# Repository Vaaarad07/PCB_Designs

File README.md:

# PCB Design Files

## Projects
- [About](#about)
- [Cyclometer](#cyclometer)
- [STM32F407 MVCU](#stm32f407-mvcu)
- [STM32F103 VCU](#stm32f103-vcu)
- [STM32F103 Inverter VCU](#stm32f103-inverter-vcu)
- [STM32F103 Test board](#stm32f103-test-board)

## About 
This repo contains the PCB files designed by [@Vaaarad07](https://github.com/Vaaarad07).
All of the designs are completely produced in KiCad 6, and each project directory contains the respective  KiCad schematic and layout files. All of the PCB projects are manufactured and tested for their respective functionalities.
I am open for any kind of feedback, suggestion or discussion.

## Cyclometer 
Cyclometer is a minimal dashhborad for bicycles used to accurately measure, store and display the speed, distance & time of the bike rides.
The board uses **STM32F446** controller.

## RP2040 

## STM32407-MVCU
This is a custom made ***4-layer*** board using ***STM32F407***, designed for [Vegapod Hyperloop](https://linktr.ee/vegapodhyperloop?fbclid=PAAabTRk45duWqCT2ES2nHaDbXQsYjndH2ZH-L-wuU1rlmgXJXES0c9xlna4E_aem_AQGd-q00TIai_09fVyH2A-mdNry7ZboQbuSte4yDi2yoPS_CXYrpFN4jU0P01uli4RE), a student team. The board is a part of a vehicle control system as the Master control Unit. The board connects to 5 separate vehicle control unit boards using DB9 cables and connectors over ***CAN bus***,which are responsible for handling their sub-system specific functions.
### Following are some of the features of the board : 
- 9-36V input power supply, which is divided into 2 separate buses of 5V and 3.3V respectively using power regulators
- 5 DB9 ports to connect the VCUs with CAN bus connections along with reserved GPIOs.
- DB9 port with RS232 to serial converter to connect an INS, [Pollux 2](https://aeronsystems.com/ins/pollux-2/) 
- On-board RF-transceiver mount.
- 7-segment display
- SD Card slot
- 5-pin Debugger/programmer headers.
- Hardware reset.
- ***UART, SPI, ADC, DAC, I2C*** Connections
- 10 user LEDs with power-on LEDs.

## STM32F103-VCU
This is a custom made 2-Layer board using 
***STM32F103***, designed for [Vegapod Hyperloop](https://linktr.ee/vegapodhyperloop?fbclid=PAAabTRk45duWqCT2ES2nHaDbXQsYjndH2ZH-L-wuU1rlmgXJXES0c9xlna4E_aem_AQGd-q00TIai_09fVyH2A-mdNry7ZboQbuSte4yDi2yoPS_CXYrpFN4jU0P01uli4RE), a student team. The board is a part of a vehicle control system as a vehicle control Unit. The board connects to the Master vehicle control unit using DB9 cable and connector over ***CAN bus*** 
### Following are some of the features of the board : 
- Powered through either the Master control unit (5V) or from on-board power input (7-36V) which is further divided into two separate buses of 5V and 3.3V respectively.
- Connects to the Master control unit over CAN bus and reserved GPIOs.
- 4-pin debugger/programmer header.
- 5 user LEDs
- Hardware reset
- ***UART, SPI, I2C, ADC*** ports.

## STM32F103-Inverter-VCU
This is a custom made 2-Layer board using 
***STM32F103***, designed for [Vegapod Hyperloop](https://linktr.ee/vegapodhyperloop?fbclid=PAAabTRk45duWqCT2ES2nHaDbXQsYjndH2ZH-L-wuU1rlmgXJXES0c9xlna4E_aem_AQGd-q00TIai_09fVyH2A-mdNry7ZboQbuSte4yDi2yoPS_CXYrpFN4jU0P01uli4RE), a student team. The board is a part of a vehicle control system as a vehicle control Unit responsible for control of the ***inverter sub-system***. The board connects to the Master vehicle control unit using DB9 cable and connector over ***CAN bus*** 
### Following are some of the features of the board : 
- Powered through either the Master control unit (5V) or from on-board power input (7-36V) which is further divided into two separate buses of 5V and 3.3V respectively.
- Connects to the Master control unit over CAN bus and reserved GPIOs.
- PWM headers connecting to the inverter driver circuit.
- 4-pin debugger/programmer header.
- Hardware reset.
- ***UART, SPI, I2C, ADC*** ports.

## STM32f103-Test-Board
This is a custom made 2-Layer board using the ***STM32F103*** , designed for [Vegapod Hyperloop](https://linktr.ee/vegapodhyperloop?fbclid=PAAabTRk45duWqCT2ES2nHaDbXQsYjndH2ZH-L-wuU1rlmgXJXES0c9xlna4E_aem_AQGd-q00TIai_09fVyH2A-mdNry7ZboQbuSte4yDi2yoPS_CXYrpFN4jU0P01uli4RE), a student team. The board is designed for testing procedures of various peripherals of the controller and verification of the designed architecture of a vehicle control system.
### Following are some of the features of the board :
- Powered through either the DB9 connector(5V) or the on-board power input (7-36V) which is further divided into two separate buses of 5V and 3.3V respectively.
- ***CAN, UART, SPI, I2C, ADC, PWM*** peripheral ports.
- 4-pin debugger/programmer header.
- 7-segment display
- Hardware reset.

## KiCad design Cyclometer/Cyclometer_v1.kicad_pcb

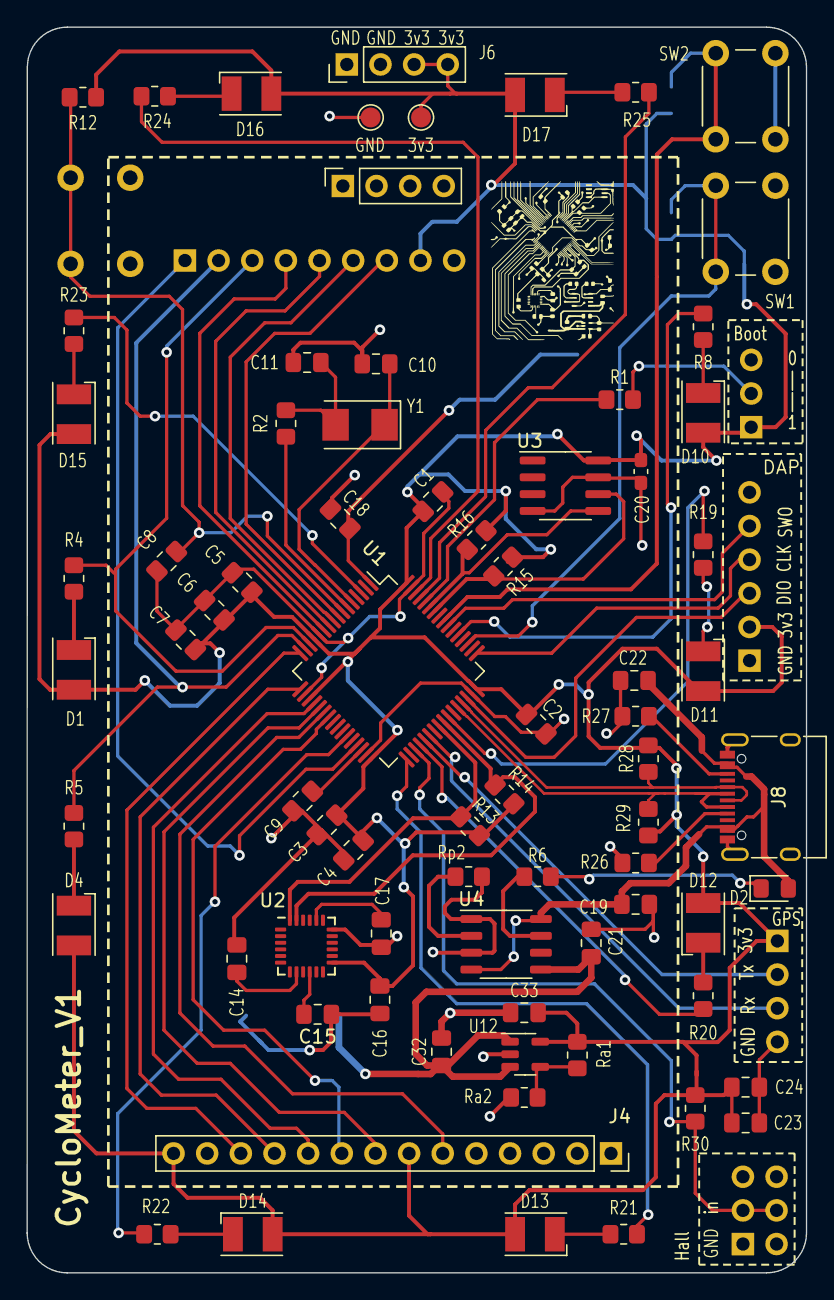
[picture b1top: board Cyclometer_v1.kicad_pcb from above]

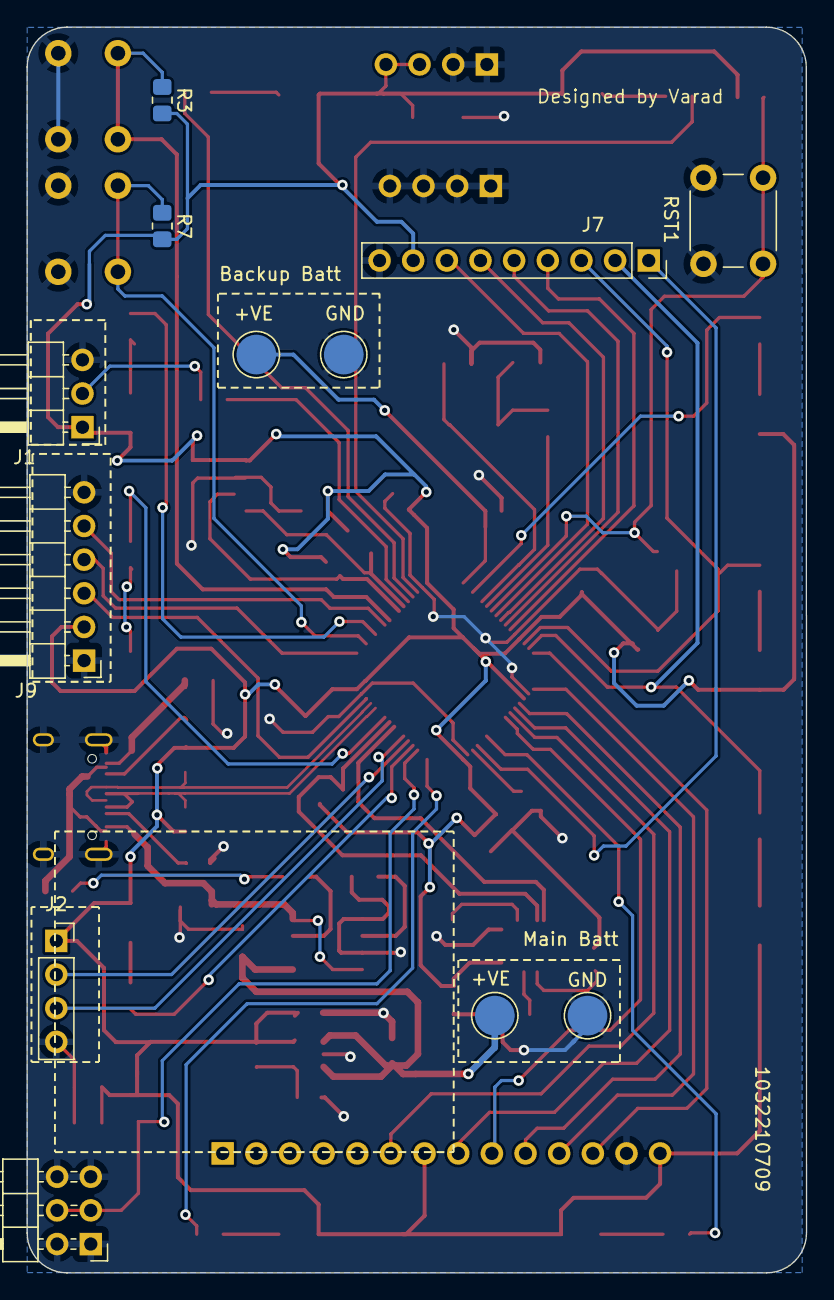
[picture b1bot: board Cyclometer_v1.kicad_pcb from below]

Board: 2 copper layers, 58.8 x 94.0 mm, 87 parts (12 on the bottom side), 66 nets.

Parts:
C1, C2, C3, C4, C5, C6, C8: 100nF; C_0805_2012Metric_Pad1.18x1.45mm_HandSolder
C7: 1uF; C_0805_2012Metric_Pad1.18x1.45mm_HandSolder
C9: 4.7uF; C_0805_2012Metric_Pad1.18x1.45mm_HandSolder
C10, C11: TBC; C_0805_2012Metric_Pad1.18x1.45mm_HandSolder
C14: 10nF; C_0805_2012Metric_Pad1.18x1.45mm_HandSolder
C15, C16, C19, C24: 0.1uF; C_0805_2012Metric_Pad1.18x1.45mm_HandSolder
C17: 2.2nF; C_0805_2012Metric_Pad1.18x1.45mm_HandSolder
C18, C21, C22, C23, C32, C33: 10uF; C_0805_2012Metric_Pad1.18x1.45mm_HandSolder
C20: 100nF; C_0603_1608Metric_Pad1.08x0.95mm_HandSolder
D1, D4, D10, D11, D12, D13, D14, D15, D16, D17: LED; LED_PLCC-2_3.4x3.0mm_KA
D2: LED; LED_0805_2012Metric_Pad1.15x1.40mm_HandSolder
J1: Conn_01x03_Male; PinHeader_1x03_P2.54mm_Horizontal
J2: GPS; PinSocket_1x04_P2.54mm_Vertical
J3: Conn_01x06_Pin; PinHeader_2x03_P2.54mm_Horizontal
J4: LCD; PinSocket_1x14_P2.54mm_Vertical
J5: LCD; PinSocket_1x04_P2.54mm_Vertical
J6: PinHeader_1x04_P2.54mm_Vertical
J7: NRF; PinSocket_1x09_P2.54mm_Vertical
J8: USB_C_Receptacle; USB_C_Receptacle_XKB_U262-16XN-4BVC11
J9: Conn_01x06_Pin; PinHeader_1x06_P2.54mm_Horizontal
R1, R3, R4, R5, R7, R8, R12, R19, R20, R21, R22, R23, R24, R25, R30: 10K; R_0805_2012Metric_Pad1.20x1.40mm_HandSolder
R2: TBC; R_0805_2012Metric_Pad1.20x1.40mm_HandSolder
R6: R_Small_US; R_0805_2012Metric_Pad1.20x1.40mm_HandSolder
R13, R14, R15, R16: 4.7k; R_0805_2012Metric_Pad1.20x1.40mm_HandSolder
R26, R27, R28, R29: 5.1k; R_0805_2012Metric_Pad1.20x1.40mm_HandSolder
RST1: SW_Push; SW_PUSH_6mm
Ra1, Ra2: R_Small_US; R_0805_2012Metric_Pad1.20x1.40mm_HandSolder
Rp2: 1K2; R_0805_2012Metric_Pad1.20x1.40mm_HandSolder
SW1, SW2: SW_Push; SW_PUSH_6mm
TP1, TP4: +VE; TestPoint_Pad_D3.0mm
TP2, TP3: GND; TestPoint_Pad_D3.0mm
TP5: GND; TestPoint_Pad_D1.5mm
TP6: 3v3; TestPoint_Pad_D1.5mm
U1: STM32F446RCTx; LQFP-64_10x10mm_P0.5mm
U2: MPU-6050; InvenSense_QFN-24_4x4mm_P0.5mm
U3: AT24CS32-SSHM; SOIC-8_3.9x4.9mm_P1.27mm
U4: TP4056; SOP-8_3.9x4.9mm_P1.27mm
U12: LDK130-ADJ_SOT23_SOT353; SOT-23-5
Y1: Crystal; Crystal_SMD_5032-2Pin_5.0x3.2mm

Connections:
+3.3V: C1.1, C2.1, C3.1, C4.1, C5.1, C6.1, C7.1, C16.2, C20.2, C23.2, C24.1, C33.2, D1.2 (A), D4.2 (A), D10.2 (A), D11.2 (A), D12.2 (A), D13.2 (A), D14.2 (A), D15.2 (A), D16.2 (A), D17.2 (A), J1.1, J2.1, J4.7, J4.14, J6.3, J6.4, J7.8, J9.2, R3.2, R7.2, R12.2, R13.2, R14.2, R15.2, R16.2, R28.2, R29.2, R30.2, Ra1.1, TP6.1, U1.13 (VDDA), U1.19 (VDD), U1.32 (VDD), U1.48 (VDD), U1.64 (VDD), U2.13 (VDD), U3.8 (VCC), U12.5 (OUT)
/MCU/EEPROM_SCL_1: R15.1, U1.58 (PB6), U3.6 (SCL)
/MCU/EEPROM_SDA_1: R16.1, U1.59 (PB7), U3.5 (SDA)
/MCU/GPS_1_Rx: J2.3, U1.38 (PC7)
/MCU/GPS_1_Tx: J2.2, U1.37 (PC6)
/MCU/HSE_IN: C10.1, U1.5 (PH0), Y1.1
/MCU/HSE_OUT: R2.2, U1.6 (PH1)
/MCU/HallEffect_ip: J3.3, J3.4, R30.1, U1.35 (PB14)
/MCU/IMU_SCL: R14.1, U1.41 (PA8), U2.23 (SCL)
/MCU/IMU_SDA: R13.1, U1.40 (PC9), U2.24 (SDA)
/MCU/LCD_Cs: J4.12, U1.16 (PA2)
/MCU/LCD_DcRs: J4.10, U1.20 (PA4)
/MCU/LCD_Miso: J4.6, U1.22 (PA6)
/MCU/LCD_Mosi: J4.9, U1.23 (PA7)
/MCU/LCD_Sck: J4.8, U1.21 (PA5)
/MCU/LCD_rst: J4.11, U1.17 (PA3)
/MCU/LED1: R8.1, U1.53 (PC12)
/MCU/LED2: R19.1, U1.42 (PA9)
/MCU/LED3: R20.1, U1.36 (PB15)
/MCU/LED4: R21.1, U1.33 (PB12)
/MCU/LED5: R22.1, U1.27 (PB1)
/MCU/LED8: R23.1, U1.3 (PC14)
/MCU/LED9: R24.1, U1.62 (PB9)
/MCU/LED10: R25.1, U1.61 (PB8)
/MCU/NRF_MISO_2: J7.5, U1.10 (PC2)
/MCU/NRF_MOSI2: J7.6, U1.9 (PC1)
/MCU/NRF_RDYN: J7.4, U1.11 (PC3)
/MCU/NRF_REQN: J7.7, U1.8 (PC0)
/MCU/NRF_SCK2: J7.1, U1.29 (PB10)
/MCU/NRF_UART_RX: J7.2, R5.1, U1.15 (PA1)
/MCU/NRF_UART_TX: J7.3, R4.1, U1.14 (PA0)
/MCU/SWCLK: J9.4, U1.49 (PA14)
/MCU/SWDIO: J9.3, U1.46 (PA13)
/MCU/SWO: J9.5, U1.55 (PB3)
/MCU/user_1: R7.1, SW1.1, U1.51 (PC10)
/MCU/user_2: R3.1, SW2.1, U1.56 (PB4)
/Power/USB_CC1: J8.B5 (CC2), R27.2
/Power/USB_CC2: J8.A5 (CC1), R26.2
Batt+: C21.1, C32.1, TP1.1, U4.5 (BAT), U12.1 (IN), U12.3 (EN)
GND: C1.2, C2.2, C3.2, C4.2, C5.2, C6.2, C7.2, C8.2, C9.2, C10.2, C11.2, C14.1, C15.1, C16.1, C17.1, C18.1, C19.2, C20.1, C21.2, C22.2, C23.1, C24.2, C32.2, C33.1, J1.3, J2.4, J3.1, J3.2, J3.5, J3.6, J4.13, J5.1, J5.2, J5.3, J5.4, J6.1, J6.2, J7.9, J8.A1 (GND), J8.A12 (GND), J8.B1 (GND), J8.B12 (GND), J8.S1 (SHIELD), J9.1, J9.6, R26.1, R27.1, RST1.1, Ra2.2, Rp2.1, SW1.2, SW2.2, TP2.1, TP3.1, TP5.1, U1.12 (VSSA), U1.18 (VSS), U1.31 (VSS), U1.47 (VSS), U1.63 (VSS), U2.18 (GND), U3.4 (GND), U3.7 (WP), U4.1 (Temp1), U4.3 (GND3), U12.2 (GND)
unnamed: C11.1, R2.1, Y1.2
unnamed: D1.1 (K), R4.2
unnamed: C19.1, C22.1, D2.2 (A), J8.A4 (VBUS), J8.A9 (VBUS), J8.B4 (VBUS), J8.B9 (VBUS), U4.4 (Vcc4), U4.8 (CE)
unnamed: D2.1 (K), R6.1
unnamed: D4.1 (K), R5.2
unnamed: D10.1 (K), R8.2
unnamed: D11.1 (K), R19.2
unnamed: D12.1 (K), R20.2
unnamed: D13.1 (K), R21.2
unnamed: D14.1 (K), R22.2
unnamed: D15.1 (K), R23.2
unnamed: D16.1 (K), R24.2
unnamed: D17.1 (K), R25.2
unnamed: J1.2, R1.1
unnamed: R1.2, U1.60 (BOOT0)
unnamed: C8.1, R12.1, RST1.2, U1.7 (NRST)
unnamed: C9.1, U1.30 (VCAP_1)
unnamed: C17.2, U2.20 (CPOUT)
unnamed: C15.2, U2.10 (REGOUT)
unnamed: C14.2, U2.8 (VLOGIC)
unnamed: R6.2, U4.7 (CHRG)
unnamed: Rp2.2, U4.2 (prog2)
unnamed: Ra1.2, Ra2.1, U12.4 (ADJ)
USB_FS_D+: J8.A6 (D+), J8.B6 (D+), R28.1, U1.45 (PA12)
USB_FS_D-: J8.A7 (D-), J8.B7 (D-), R29.1, U1.44 (PA11)
Vbat: C18.2, TP4.1, U1.1 (VBAT)

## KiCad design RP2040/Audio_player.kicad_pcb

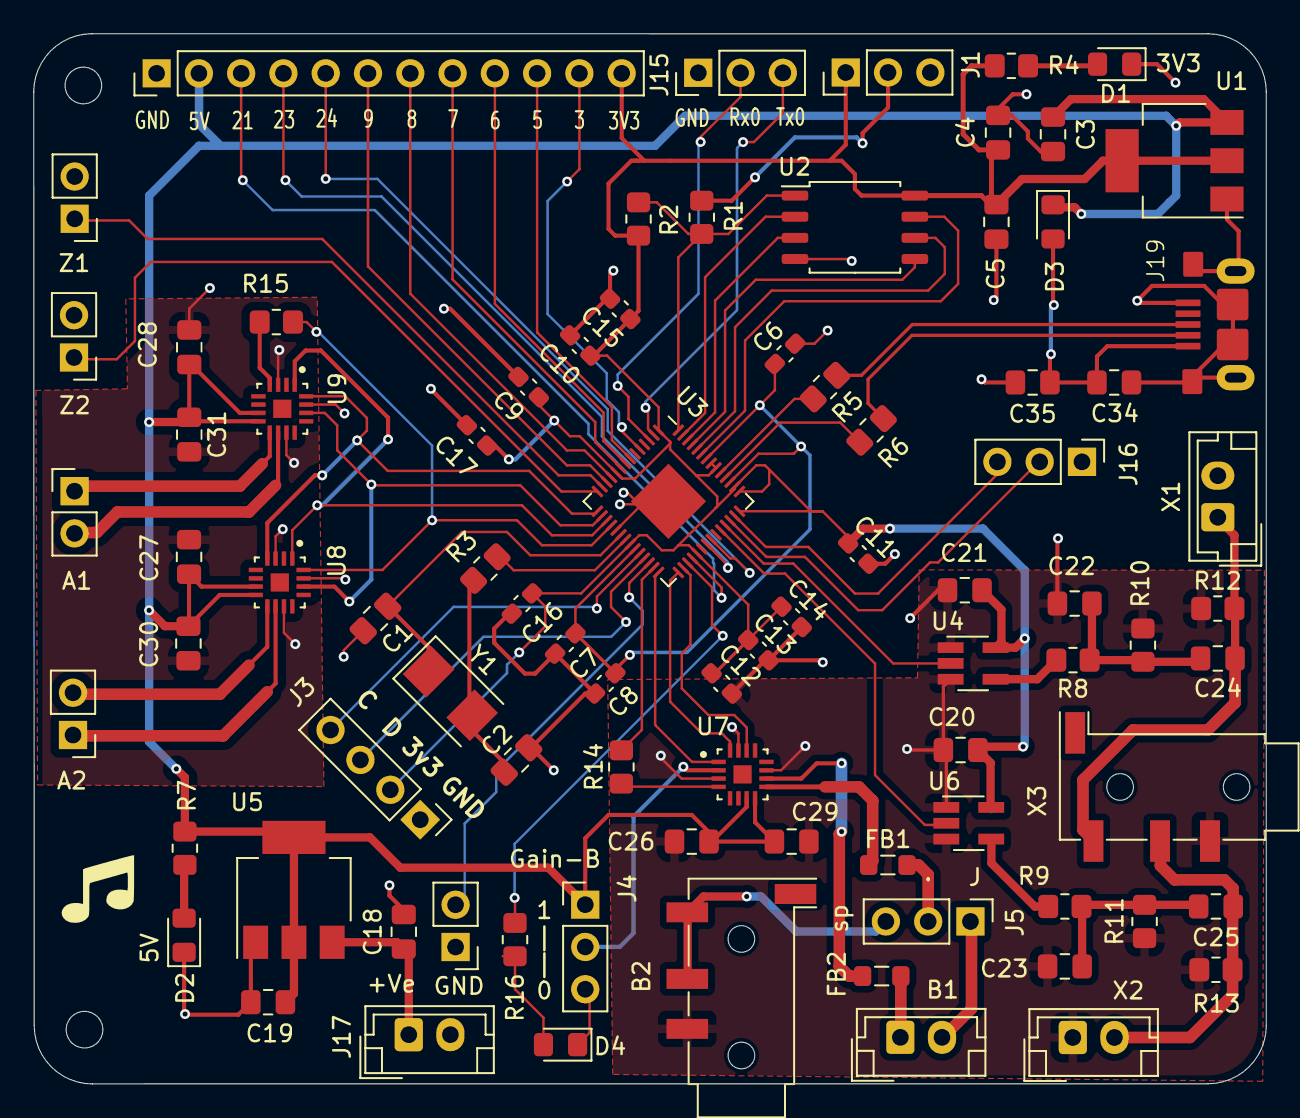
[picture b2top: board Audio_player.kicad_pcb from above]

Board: 2 copper layers, 74.0 x 63.1 mm, 86 parts (0 on the bottom side), 71 nets.

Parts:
A1, A2: Conn_01x02_Pin; PinHeader_1x02_P2.54mm_Vertical
B1: Conn_01x02_Pin; JST_EH_B2B-EH-A_1x02_P2.50mm_Vertical
B2: AudioJack4; Jack_3.5mm_KoreanHropartsElec_PJ-320D-4A_Horizontal
C1, C2, C5, C22, C23, C34: 100n; C_0805_2012Metric_Pad1.18x1.45mm_HandSolder
C3, C4, C18, C19, C20, C21, C26, C27, C28, C35: 10u; C_0805_2012Metric_Pad1.18x1.45mm_HandSolder
C6, C8, C9, C10, C12, C13, C14, C15, C16, C17: 100n; C_0603_1608Metric_Pad1.08x0.95mm_HandSolder
C7, C11: 1u; C_0603_1608Metric_Pad1.08x0.95mm_HandSolder
C24, C25: 47u; C_0805_2012Metric_Pad1.18x1.45mm_HandSolder
C29, C30, C31: 0.1u; C_0805_2012Metric_Pad1.18x1.45mm_HandSolder
D1, D2, D4: LED; LED_0805_2012Metric_Pad1.15x1.40mm_HandSolder
D3: D; D_0805_2012Metric_Pad1.15x1.40mm_HandSolder
FB1, FB2: FerriteBead_Small; L_0805_2012Metric_Pad1.05x1.20mm_HandSolder
H1, H4: MountingHole_Pad; MountingHole_2.2mm_M2
J1, J4, J5, J15, J16: Conn_01x03_Pin; PinHeader_1x03_P2.54mm_Vertical
J2: Conn_01x12_Pin; PinHeader_1x12_P2.54mm_Vertical
J3: Conn_01x04_Pin; PinHeader_1x04_P2.54mm_Vertical
J6: Conn_01x02_Pin; PinHeader_1x02_P2.54mm_Vertical
J17: Conn_01x02_Pin; JST_EH_B2B-EH-A_1x02_P2.50mm_Vertical
J19: USB3076-XX-X_REVC5; USB-B_varad
R1, R3, R4, R7, R16: 1k; R_0805_2012Metric_Pad1.20x1.40mm_HandSolder
R2: DNF; R_0805_2012Metric_Pad1.20x1.40mm_HandSolder
R5, R6: 27.4; R_0805_2012Metric_Pad1.20x1.40mm_HandSolder
R8, R9: 220; R_0805_2012Metric_Pad1.20x1.40mm_HandSolder
R10, R11: 100; R_0805_2012Metric_Pad1.20x1.40mm_HandSolder
R12, R13: 1.8k; R_0805_2012Metric_Pad1.20x1.40mm_HandSolder
R14: 300k; R_0805_2012Metric_Pad1.20x1.40mm_HandSolder
R15: 69.8k; R_0805_2012Metric_Pad1.20x1.40mm_HandSolder
U1: AMS1117-3.3; SOT-223-3_TabPin2
U2: W25Q128JVS; SOIC-8_5.23x5.23mm_P1.27mm
U3: RP2040; QFN-56-1EP_7x7mm_P0.4mm_EP3.2x3.2mm
U4, U6: 74LVC1G125; SOT-23-5_HandSoldering
U5: AMS1117-5.0; SOT-223-3_TabPin2
U7, U8, U9: MAX98357AETE_; QFN50P300X300X80-17N
X1, X2: Conn_01x02_Pin; JST_EH_B2B-EH-A_1x02_P2.50mm_Vertical
X3: AudioJack4; Jack_3.5mm_KoreanHropartsElec_PJ-320D-4A_Horizontal
Y1: Crystal; Crystal_SMD_5032-2Pin_5.0x3.2mm
Z1, Z2: Conn_01x02_Pin; PinHeader_1x02_P2.54mm_Vertical

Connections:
+3V3: C4.1, C5.1, C9.1, C10.1, C11.1, C12.1, C13.1, C14.1, C15.1, C16.1, C17.1, C20.1, C21.1, J1.1, J2.12, J3.2, R2.2, R4.1, U1.2 (VO), U2.8 (VCC), U3.1 (IOVDD), U3.10 (IOVDD), U3.22 (IOVDD), U3.33 (IOVDD), U3.42 (IOVDD), U3.43 (ADC_AVDD), U3.44 (VREG_IN), U3.48 (USB_VDD), U3.49 (IOVDD), U4.5 (VCC), U6.5 (VCC)
+5V: C3.1, C19.1, C26.1, C27.1, C28.1, C29.1, C30.1, C31.1, D3.1 (K), J2.2, J4.1, R7.1, U1.3 (VI), U5.2 (VO), U7.7 (VDD), U7.8 (VDD), U8.7 (VDD), U8.8 (VDD), U9.7 (VDD), U9.8 (VDD)
+BATT: C18.1, J17.1, U5.3 (VI)
/mcu/ADC0: U3.38 (GPIO26_ADC0), U6.2
/mcu/ADC1: U3.39 (GPIO27_ADC1), U4.2
/mcu/ADC2: J16.2, U3.40 (GPIO28_ADC2)
/mcu/ADC3: J16.3, U3.41 (GPIO29_ADC3)
/mcu/BCLK_1_19: U3.29 (GPIO18), U7.16 (BCLK)
/mcu/BCLK_2_12: U3.15 (GPIO12), U8.4 (~SD_MODE), U9.16 (BCLK)
/mcu/Din_1_17: U3.28 (GPIO17), U7.1 (DIN)
/mcu/Din_2_14: U3.17 (GPIO14), U8.1 (DIN), U9.1 (DIN)
/mcu/LRCLK_1_18: U3.30 (GPIO19), U7.14 (LRCLK)
/mcu/LRCLK_2_13: U3.16 (GPIO13), U8.14 (LRCLK), U9.14 (LRCLK)
/mcu/QSPI_CLK: U2.6 (CLK), U3.52 (QSPI_SCLK)
/mcu/QSPI_SD0: U2.5 (DI(IO0)), U3.53 (QSPI_SD0)
/mcu/QSPI_SD1: U2.2 (DO(IO1)), U3.55 (QSPI_SD1)
/mcu/QSPI_SD2: U2.3 (IO2), U3.54 (QSPI_SD2)
/mcu/QSPI_SD3: U2.7 (IO3), U3.51 (QSPI_SD3)
/mcu/QSPI_SS: R1.2, R2.1, U2.1 (~CS), U3.56 (QSPI_SS)
/mcu/SD_1_16: R14.2, U3.27 (GPIO16)
/mcu/SD_2_15: R15.2, U3.18 (GPIO15), U8.16 (BCLK)
/mcu/USB_BOOT: J1.2, R1.1
/mcu/USB_D+: J19.3 (D+), R5.1
/mcu/USB_D-: J19.2 (D-), R6.1
/mcu/gp10: U3.13 (GPIO10), Z1.1
/mcu/gp11: U3.14 (GPIO11), Z2.1
/mcu/gp20: R16.1, U3.31 (GPIO20)
/mcu/gp21: J2.3, U3.32 (GPIO21)
/mcu/gp23: J2.4, U3.35 (GPIO23)
/mcu/gp24: J2.5, U3.36 (GPIO24)
/mcu/pcm_+ve: FB1.2, J5.2
/mcu/pwm_l: C24.1, R12.2, X1.1, X3.T
/mcu/pwm_r: C25.1, R13.2, X2.2, X3.R1
/mcu/run: J6.2, U3.26 (RUN)
/mcu/swclk: J3.4, U3.24 (SWCLK)
/mcu/swd: J3.3, U3.25 (SWD)
/mcu/uart0_rx: J15.2, U3.3 (GPIO1)
/mcu/uart0_tx: J15.3, U3.2 (GPIO0)
/mcu/xin: C1.1, U3.20 (XIN), Y1.1
/mcu/xout: R3.2, U3.21 (XOUT)
GND: B2.R2, C1.2, C2.2, C3.2, C4.2, C5.2, C6.2, C7.2, C8.2, C9.2, C10.2, C11.2, C12.2, C13.2, C14.2, C15.2, C16.2, C17.2, C18.2, C19.2, C20.2, C21.2, C22.2, C23.2, C26.2, C27.2, C28.2, C29.2, C30.2, C31.2, C34.2, C35.2, D1.1 (K), D2.1 (K), D4.1 (K), J1.3, J2.1, J3.1, J4.3, J6.1, J15.1, J16.1, J17.2, J19.5 (GND), J19.6 (SHIELD), J19.7 (SHIELD), J19.8 (SHIELD), J19.9 (SHIELD), J19.10 (SHIELD), R10.1, R11.1, R12.1, R13.1, U1.1 (GND), U2.4 (GND), U3.19 (TESTEN), U3.57 (GND), U4.1, U4.3 (GND), U5.1 (GND), U6.1, U6.3 (GND), U7.3 (GND), U7.11 (GND), U7.15 (GND), U8.3 (GND), U8.11 (GND), U8.15 (GND), U9.3 (GND), U9.11 (GND), U9.15 (GND), X1.2, X2.1, X3.R2, Z1.2, Z2.2
unnamed: A1.1, U9.9 (OUTP)
unnamed: A1.2, U9.10 (OUTN)
unnamed: A2.1, U8.10 (OUTN)
unnamed: A2.2, U8.9 (OUTP)
unnamed: B1.1, FB2.2
unnamed: B1.2, J5.1
unnamed: C2.1, R3.1, Y1.2
unnamed: C22.1, C24.2, R8.1, R10.2
unnamed: C23.1, C25.2, R9.1, R11.2
unnamed: D1.2 (A), R4.2
unnamed: D2.2 (A), R7.2
unnamed: D4.2 (A), R16.2
unnamed: J2.6, U3.12 (GPIO9)
unnamed: J2.7, U3.11 (GPIO8)
unnamed: J2.8, U3.9 (GPIO7)
unnamed: J2.9, U3.8 (GPIO6)
unnamed: J2.10, U3.7 (GPIO5)
unnamed: J2.11, U3.5 (GPIO3)
unnamed: J4.2, U7.2 (GAIN_SLOT)
unnamed: B2.R1, B2.T, J5.3
unnamed: R8.2, U4.4
unnamed: R9.2, U6.4
unnamed: R6.2, U3.46 (USB_DM)
unnamed: R5.2, U3.47 (USB_DP)
unnamed: C6.1, C7.1, C8.1, U3.23 (DVDD), U3.45 (VREG_VOUT), U3.50 (DVDD)
unnamed: FB2.1, U7.10 (OUTN)
unnamed: FB1.1, U7.9 (OUTP)
unnamed: R14.1, U7.4 (~SD_MODE)
unnamed: R15.1, U9.4 (~SD_MODE)
VBUS: C34.1, C35.1, D3.2 (A), J19.1 (VBUS)

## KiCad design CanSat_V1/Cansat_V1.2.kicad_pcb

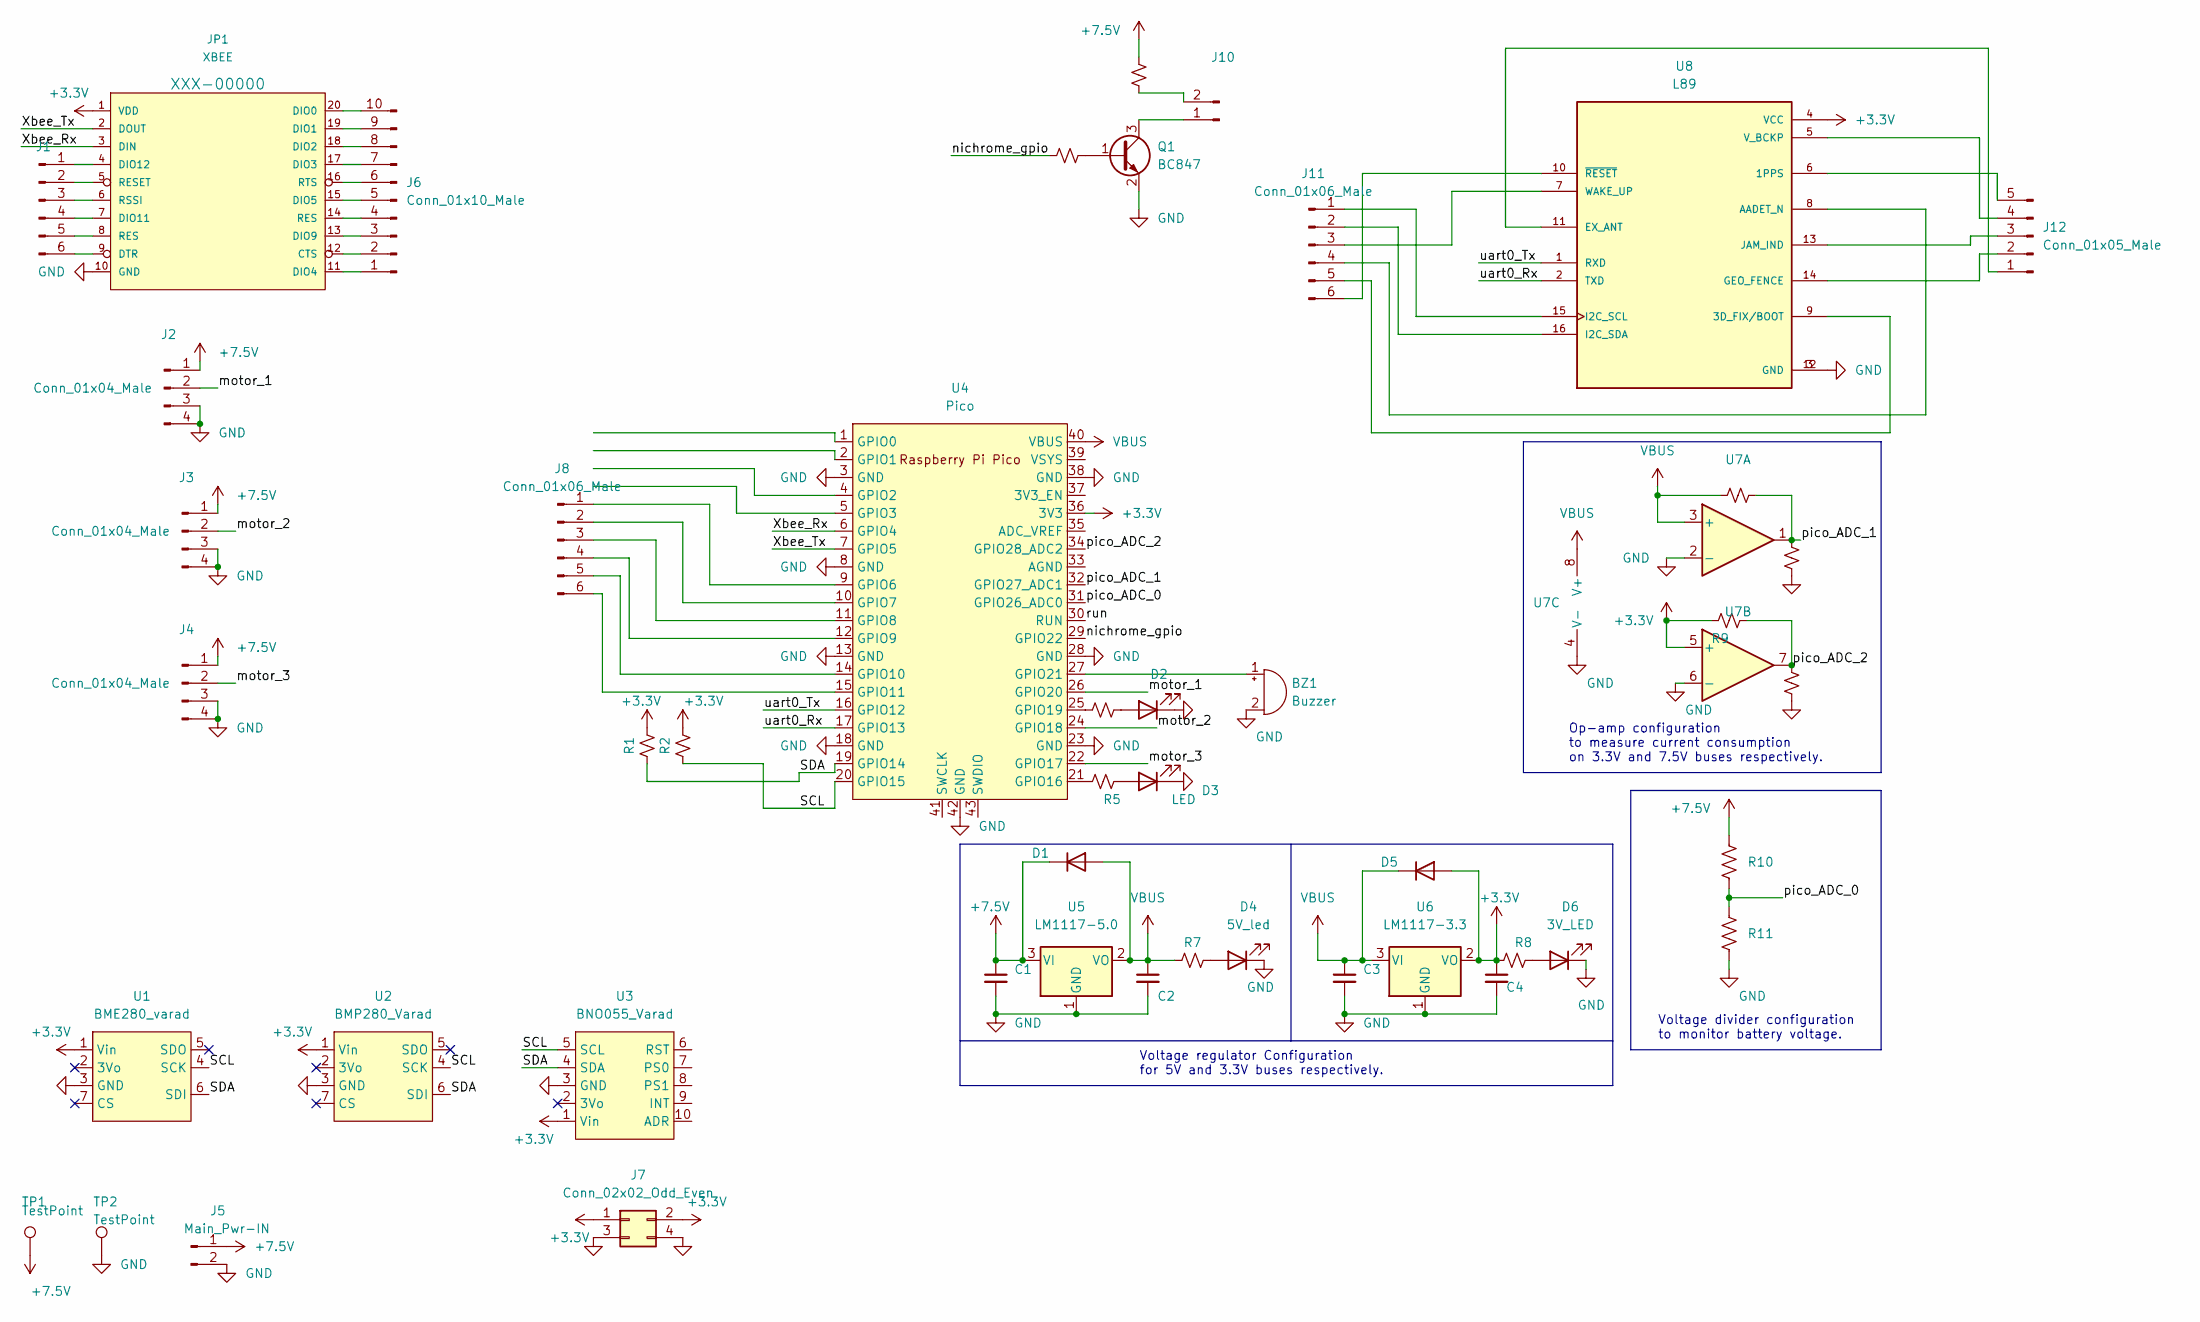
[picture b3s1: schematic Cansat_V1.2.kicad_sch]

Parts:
BZ1: Buzzer; Buzzer_12x9.5RM7.6
C1, C2, C3, C4: C_Small; C_0805_2012Metric_Pad1.18x1.45mm_HandSolder
D1, D5: 1N4007; D_DO-41_SOD81_P10.16mm_Horizontal
D2, D3: LED; LED_0805_2012Metric_Pad1.15x1.40mm_HandSolder
D4: 5V_led; LED_0805_2012Metric_Pad1.15x1.40mm_HandSolder
D6: 3V_LED; LED_0805_2012Metric_Pad1.15x1.40mm_HandSolder
J1, J8, J11: Conn_01x06_Male; PinHeader_1x06_P2.54mm_Vertical
J2, J3, J4: Conn_01x04_Male; PhoenixContact_MSTBVA_2,5_4-G-5,08_1x04_P5.08mm_Vertical
J5: Main_Pwr-IN; PhoenixContact_MSTBVA_2,5_2-G-5,08_1x02_P5.08mm_Vertical
J6: Conn_01x10_Male; PinHeader_1x10_P2.54mm_Vertical
J7: Conn_02x02_Odd_Even; PinHeader_1x04_P2.54mm_Vertical
J10: nichrome; PhoenixContact_MSTBVA_2,5_2-G-5,08_1x02_P5.08mm_Vertical
J12: Conn_01x05_Male; PinHeader_1x05_P2.54mm_Vertical
JP1: XBEE; XBEE-SILK
Q1: BC847; SOT-23
R1, R2, R3, R4, R5, R6, R7, R8, R9, R12, R13, R14: R_Small_US; R_0805_2012Metric_Pad1.20x1.40mm_HandSolder
R10, R11: R_US; R_2512_6332Metric_Pad1.40x3.35mm_HandSolder
TP1, TP2: TestPoint; TestPoint_Pad_D4.0mm
U1: BME280_varad; BME280_Varad
U2: BMP280_Varad
U3: BNO055_Varad
U4: Pico; RPi_Pico_SMD_TH
U5: LM1117-5.0; SOT-223-3_TabPin2
U6: LM1117-3.3; SOT-223-3_TabPin2
U7: MCP6002-xSN; SuperSOT-8
U8: L89; XCVR_L89; PARTREV 1.1

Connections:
+3.3V: C4.1, D5.2 (A), J7.1, J7.2, JP1.1 (VDD), R1.1, R2.1, R8.2, R9.1, U1.1 (Vin), U2.1 (Vin), U3.1 (Vin), U4.36 (3V3), U6.2 (VO), U7.5 (+), U8.4 (VCC)
+7.5V: C1.1, D1.1 (K), J2.1, J3.1, J4.1, J5.1, R6.2, R10.1, TP1.1, U5.3 (VI)
/SCL: R2.2, U1.4 (SCK), U2.4 (SCK), U3.5 (SCL), U4.20 (GPIO15)
/SDA: R1.2, U1.6 (SDI), U2.6 (SDI), U3.4 (SDA), U4.19 (GPIO14)
/Xbee_Rx: JP1.3 (DIN), U4.6 (GPIO4)
/Xbee_Tx: JP1.2 (DOUT), U4.7 (GPIO5)
/motor_1: J2.2, U4.26 (GPIO20)
/motor_2: J3.2, U4.24 (GPIO18)
/motor_3: J4.2, U4.22 (GPIO17)
/nichrome_gpio: R3.1, U4.29 (GPIO22)
/pico_ADC_0: R10.2, R11.1, U4.31 (GPIO26_ADC0)
/pico_ADC_1: R12.2, R13.2, U4.32 (GPIO27_ADC1), U7.1
/pico_ADC_2: R9.2, R14.2, U4.34 (GPIO28_ADC2), U7.7
/run: U4.30 (RUN)
/uart0_Rx: U4.17 (GPIO13), U8.2 (TXD)
/uart0_Tx: U4.16 (GPIO12), U8.1 (RXD)
GND: BZ1.2 (+), C1.2, C2.2, C3.2, C4.2, D2.1 (K), D3.1 (K), D4.1 (K), D6.1 (K), J2.3, J2.4, J3.3, J3.4, J4.3, J4.4, J5.2, J7.3, J7.4, JP1.10 (GND), Q1.2 (E), R11.2, R13.1, R14.1, TP2.1, U1.3 (GND), U2.3 (GND), U3.3 (GND), U4.3 (GND), U4.8 (GND), U4.13 (GND), U4.18 (GND), U4.23 (GND), U4.28 (GND), U4.38 (GND), U4.42 (GND), U5.1 (GND), U6.1 (GND), U7.2 (-), U7.4 (V-), U7.6 (-), U8.3 (GND), U8.12 (GND)
unnamed: BZ1.1 (-), U4.27 (GPIO21)
unnamed: D2.2 (A), R4.1
unnamed: D3.2 (A), R5.1
unnamed: D4.2 (A), R7.1
unnamed: D6.2 (A), R8.1
unnamed: J1.1, JP1.4 (DIO12)
unnamed: J1.2, JP1.5 (RESET)
unnamed: J1.3, JP1.6 (RSSI)
unnamed: J1.4, JP1.7 (DIO11)
unnamed: J1.5, JP1.8 (RES)
unnamed: J1.6, JP1.9 (DTR)
unnamed: J6.1, JP1.11 (DIO4)
unnamed: J6.2, JP1.12 (CTS)
unnamed: J6.3, JP1.13 (DIO9)
unnamed: J6.4, JP1.14 (RES)
unnamed: J6.5, JP1.15 (DIO5)
unnamed: J6.6, JP1.16 (RTS)
unnamed: J6.7, JP1.17 (DIO3)
unnamed: J6.8, JP1.18 (DIO2)
unnamed: J6.9, JP1.19 (DIO1)
unnamed: J6.10, JP1.20 (DIO0)
unnamed: J8.1, U4.9 (GPIO6)
unnamed: J8.2, U4.10 (GPIO7)
unnamed: J8.3, U4.11 (GPIO8)
unnamed: J8.4, U4.12 (GPIO9)
unnamed: J8.5, U4.14 (GPIO10)
unnamed: J8.6, U4.15 (GPIO11)
unnamed: J10.1, Q1.3 (C)
unnamed: J10.2, R6.1
unnamed: J11.1, U8.15 (I2C_SCL)
unnamed: J11.2, U8.16 (I2C_SDA)
unnamed: J11.3, U8.7 (WAKE_UP)
unnamed: J11.4, U8.8 (AADET_N)
unnamed: J11.5, U8.9 (3D_FIX/BOOT)
unnamed: J11.6, U8.10 (~RESET)
unnamed: J12.1, U8.11 (EX_ANT)
unnamed: J12.2, U8.14 (GEO_FENCE)
unnamed: J12.3, U8.13 (JAM_IND)
unnamed: J12.4, U8.5 (V_BCKP)
unnamed: J12.5, U8.6 (1PPS)
unnamed: Q1.1 (B), R3.2
unnamed: R4.2, U4.25 (GPIO19)
unnamed: R5.2, U4.21 (GPIO16)
VBUS: C2.1, C3.1, D1.2 (A), D5.1 (K), R7.2, R12.1, U4.40 (VBUS), U5.2 (VO), U6.3 (VI), U7.3 (+), U7.8 (V+)

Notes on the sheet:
Op-amp configuration to measure current consumption on 3.3V and 7.5V buses respectively.
Voltage divider configuration to monitor battery voltage.
Voltage regulator Configuration for 5V and 3.3V buses respectively.

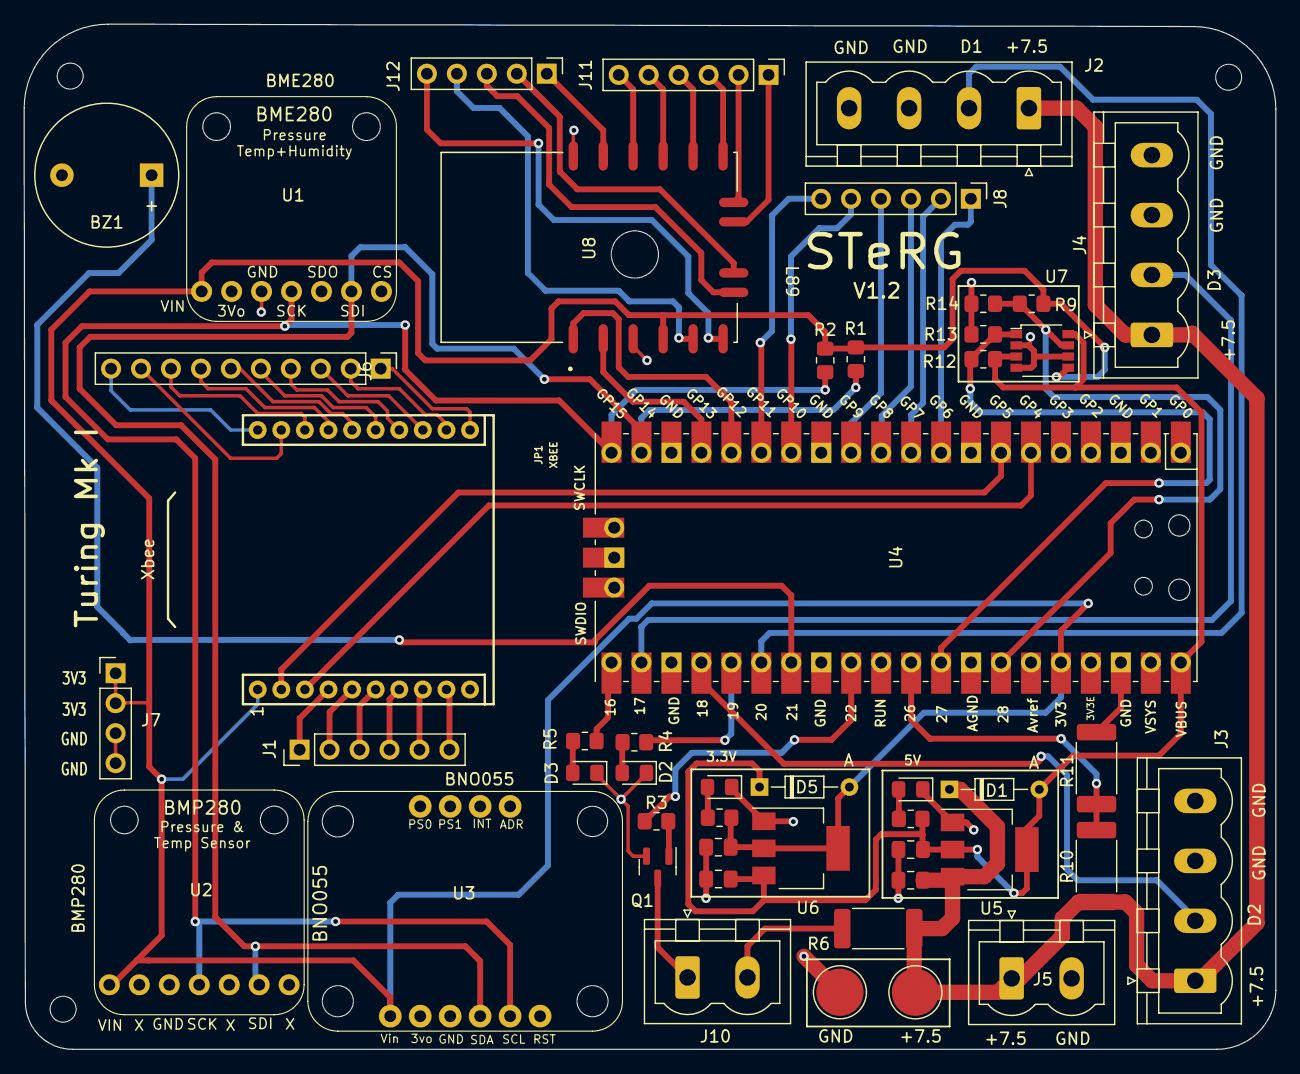
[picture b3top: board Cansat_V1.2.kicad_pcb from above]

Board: 2 copper layers, 106.1 x 86.9 mm, 48 parts (0 on the bottom side), 60 nets.

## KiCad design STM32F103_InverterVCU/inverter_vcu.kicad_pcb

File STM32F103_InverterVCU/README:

This folder contains KiCad PCB files for a custom Board.

This is a 2 layer STM32F103C8T6 custom board used as a VCU in a vehicle control application.
The board connects to a Master Vehicle control unit a through DB9 connector over the CAN bus. 
Following are some of the features of the board -
	 Powered through the MVCU (Master board) or from power input (7-36V)
	 Separate 5V and 3.3V buses
	 CAN bus
	 Generation of SPWM for inverter
	 4-pin debugger/programmer connector
	 UART, SPI, I2C, ADC ports

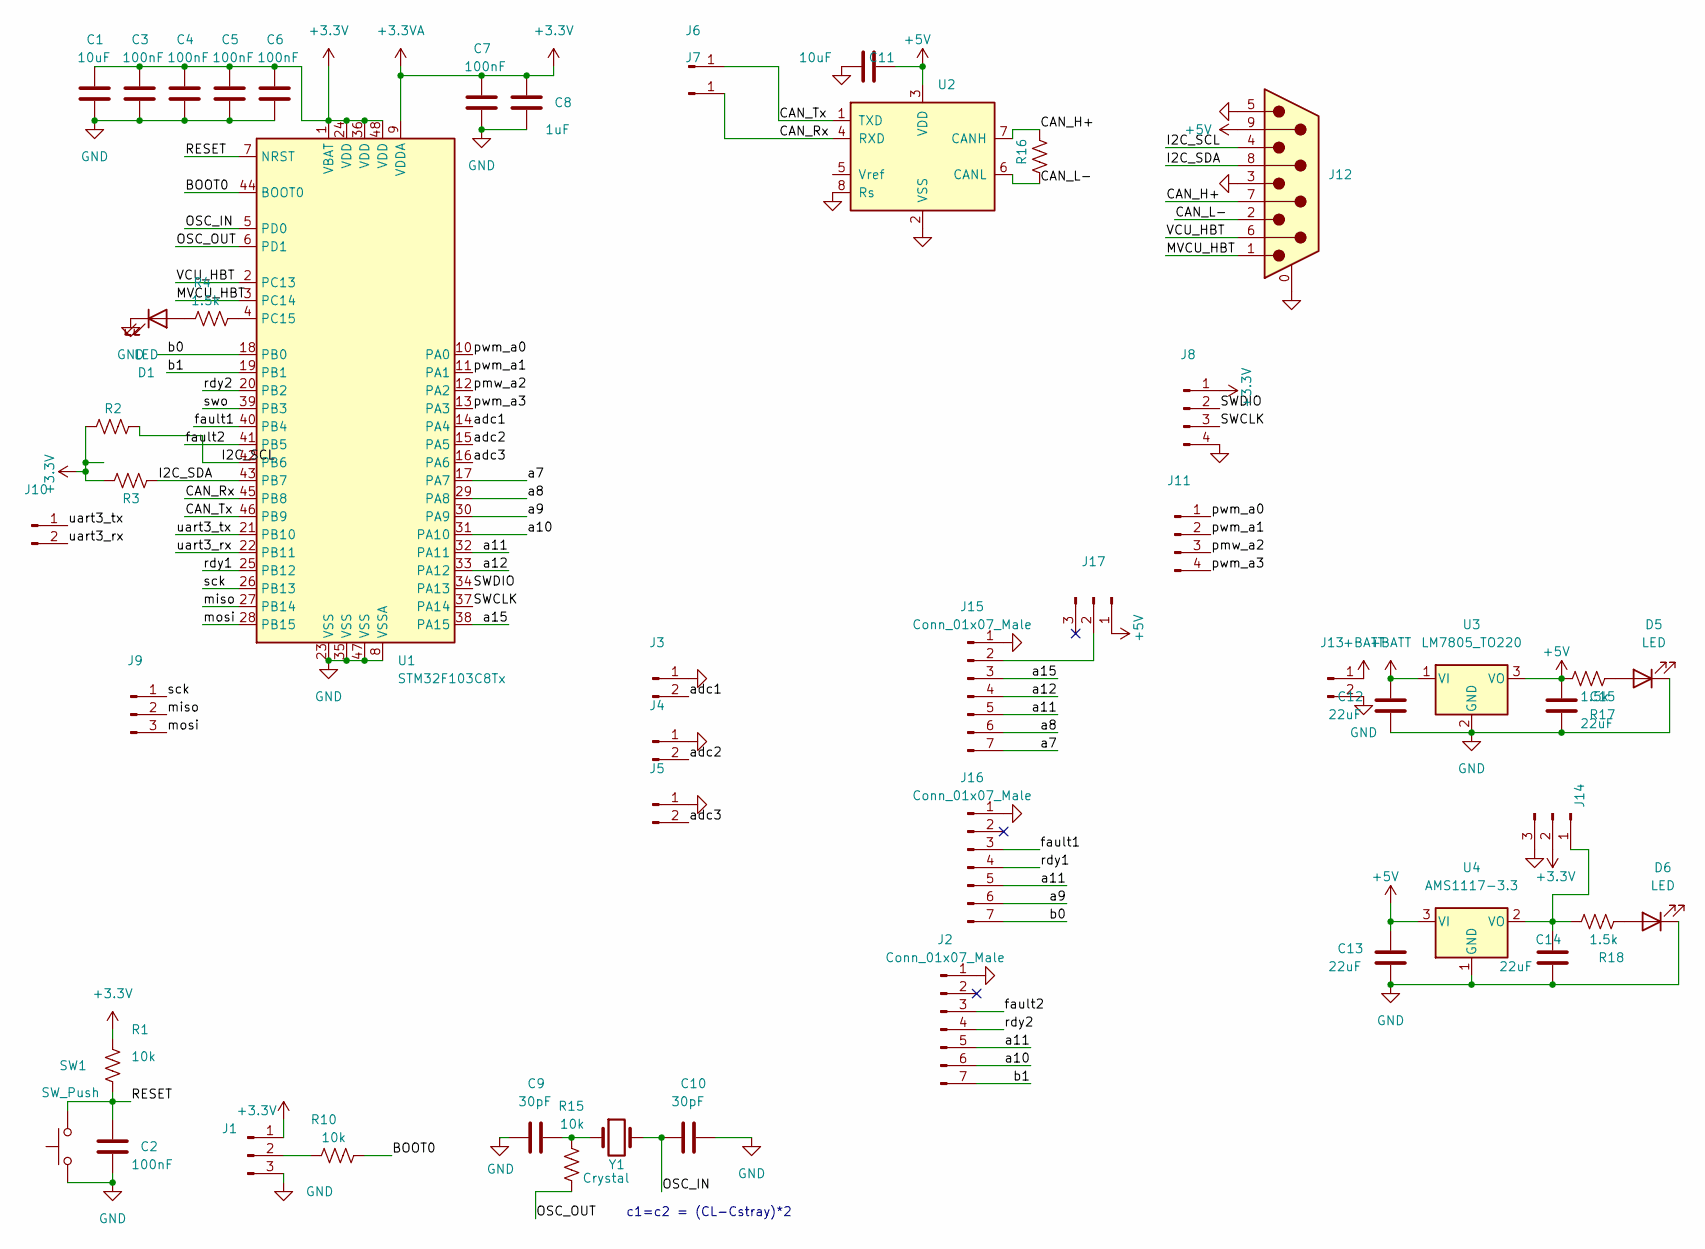
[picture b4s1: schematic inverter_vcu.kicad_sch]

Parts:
C1, C11: 10uF; C_0805_2012Metric_Pad1.18x1.45mm_HandSolder
C2, C3, C4, C5, C6, C7: 100nF; C_0805_2012Metric_Pad1.18x1.45mm_HandSolder
C8: 1uF; C_0805_2012Metric_Pad1.18x1.45mm_HandSolder
C9, C10: 30pF; C_0805_2012Metric_Pad1.18x1.45mm_HandSolder
C12: 22uF; CP_Radial_D5.0mm_P2.50mm
C13, C14: 22uF; C_0805_2012Metric_Pad1.18x1.45mm_HandSolder
C15: 22uF; CP_Radial_D5.0mm_P2.00mm
D1, D5, D6: LED; LED_0805_2012Metric_Pad1.15x1.40mm_HandSolder
J1, J9, J14, J17: Conn_01x03_Male; PinHeader_1x03_P2.54mm_Vertical
J2, J15, J16: Conn_01x07_Male; JST_EH_B7B-EH-A_1x07_P2.50mm_Vertical
J3, J4, J5: Conn_01x02_Male; JST_NV_B02P-NV_1x02_P5.00mm_Vertical
J6, J7: Conn_01x01_Male; PinHeader_1x01_P2.54mm_Vertical
J8, J11: Conn_01x04_Male; PinHeader_1x04_P2.54mm_Vertical
J10: Conn_01x02_Male; PinHeader_1x02_P2.54mm_Vertical
J12: DB9_Male_MountingHoles; DSUB-9_Male_Horizontal_P2.77x2.84mm_EdgePinOffset4.94mm_Hou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
J13: Conn_01x02_Male; PhoenixContact_MSTBVA_2,5_2-G-5,08_1x02_P5.08mm_Vertical
R1, R10, R15: 10k; R_0805_2012Metric_Pad1.20x1.40mm_HandSolder
R2, R3, R4, R16, R17, R18: 1.5k; R_0805_2012Metric_Pad1.20x1.40mm_HandSolder
SW1: SW_Push; SW_PUSH_6mm_H5mm
U1: STM32F103C8Tx; LQFP-48_7x7mm_P0.5mm
U2: MCP2551-I-SN; SOIC-8_3.9x4.9mm_P1.27mm
U3: LM7805_TO220; TO-220-3_Vertical
U4: AMS1117-3.3; SOT-223-3_TabPin2
Y1: Crystal; Crystal_HC49-U_Vertical

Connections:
+3.3V: C1.1, C3.1, C4.1, C5.1, C6.1, C7.1, C8.1, J1.1, J8.1, J14.2, R1.1, R2.2, R3.2, U1.1 (VBAT), U1.9 (VDDA), U1.24 (VDD), U1.36 (VDD), U1.48 (VDD)
+5V: C11.2, C13.1, C15.1, J12.9, J17.1, R17.2, U2.3 (VDD), U3.3 (VO), U4.3 (VI)
+BATT: C12.1, J13.1, U3.1 (VI)
/BOOT0: R10.2, U1.44 (BOOT0)
/CAN_H+: J12.7, R16.1, U2.7 (CANH)
/CAN_L-: J12.2, R16.2, U2.6 (CANL)
/CAN_Rx: J7.1, U1.45 (PB8), U2.4 (RXD)
/CAN_Tx: J6.1, U1.46 (PB9), U2.1 (TXD)
/I2C_SCL: J12.4, R2.1, U1.42 (PB6)
/I2C_SDA: J12.8, R3.1, U1.43 (PB7)
/MVCU_HBT: J12.1, U1.3 (PC14)
/OSC_IN: C10.2, U1.5 (PD0), Y1.2
/OSC_OUT: R15.1, U1.6 (PD1)
/RESET: C2.1, R1.2, SW1.2, U1.7 (NRST)
/SWCLK: J8.3, U1.37 (PA14)
/SWDIO: J8.2, U1.34 (PA13)
/VCU_HBT: J12.6, U1.2 (PC13)
/a7: J15.7, U1.17 (PA7)
/a8: J15.6, U1.29 (PA8)
/a9: J16.6, U1.30 (PA9)
/a10: J2.6, U1.31 (PA10)
/a11: J2.5, J15.5, J16.5, U1.32 (PA11)
/a12: J15.4, U1.33 (PA12)
/a15: J15.3, U1.38 (PA15)
/adc1: J3.2, U1.14 (PA4)
/adc2: J4.2, U1.15 (PA5)
/adc3: J5.2, U1.16 (PA6)
/b0: J16.7, U1.18 (PB0)
/b1: J2.7, U1.19 (PB1)
/fault1: J16.3, U1.40 (PB4)
/fault2: J2.3, U1.41 (PB5)
/miso: J9.2, U1.27 (PB14)
/mosi: J9.3, U1.28 (PB15)
/pmw_a2: J11.3, U1.12 (PA2)
/pwm_a0: J11.1, U1.10 (PA0)
/pwm_a1: J11.2, U1.11 (PA1)
/pwm_a3: J11.4, U1.13 (PA3)
/rdy1: J16.4, U1.25 (PB12)
/rdy2: J2.4, U1.20 (PB2)
/sck: J9.1, U1.26 (PB13)
/swo: U1.39 (PB3)
/uart3_rx: J10.2, U1.22 (PB11)
/uart3_tx: J10.1, U1.21 (PB10)
GND: C1.2, C2.2, C3.2, C4.2, C5.2, C6.2, C7.2, C8.2, C9.2, C10.1, C11.1, C12.2, C13.2, C14.2, C15.2, D1.1 (K), D5.1 (K), D6.1 (K), J1.3, J2.1, J3.1, J4.1, J5.1, J8.4, J12.0 (PAD), J12.3, J12.5, J13.2, J14.3, J15.1, J16.1, SW1.1, U1.8 (VSSA), U1.23 (VSS), U1.35 (VSS), U1.47 (VSS), U2.2 (VSS), U2.8 (Rs), U3.2 (GND), U4.1 (GND); also elsewhere on the board
unnamed: C9.1, R15.2, Y1.1
unnamed: C14.1, J14.1, R18.2, U4.2 (VO)
unnamed: D1.2 (A), R4.1
unnamed 47: D5.2 (A), R17.1; also elsewhere on the board
unnamed 48: D6.2 (A), R18.1; also elsewhere on the board
unnamed: J1.2, R10.1
unnamed: J15.2, J17.2
unnamed: R4.2, U1.4 (PC15)

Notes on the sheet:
c1=c2 = (CL-Cstray)*2
